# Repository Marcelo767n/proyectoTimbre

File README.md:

# 🔔 Proyecto Timbre Inteligente

Repositorio oficial con la documentación, diseño y código del prototipo de timbre inteligente. Este proyecto se desarrolla para las materias de **Sistemas Embebidos 2** y **Prototipado Rápido**.

---

## 🎯 Objetivo del Proyecto

Diseñar y construir el prototipo de un timbre inteligente basado en una placa de circuito impreso (PCB) personalizada. El sistema captura la presencia de visitantes y gestiona la información de forma remota a través de una interfaz web centralizada.

---

## ⚙️ Arquitectura del Sistema

El proyecto destaca por su capacidad de comunicación remota. Los módulos **no necesitan estar conectados a la misma red Wi-Fi**, ya que la transferencia de datos se realiza a través de Internet.

### 1. Módulo del Timbre (Cliente)
* **Hardware:** ESP32-CAM integrado en una PCB propia diseñada en **KiCad**.
* **Firmware:** Desarrollado en el framework profesional **ESP-IDF** utilizando el entorno de **PlatformIO**.
* **Función:** Al presionar el timbre, el dispositivo se conecta a la red Wi-Fi local (Red A), captura una fotografía del visitante y la envía mediante una petición **HTTP POST** hacia el servidor remoto.

### 2. Módulo de Gestión (Servidor e Interfaz Web)
* **Hardware:** Raspberry Pi.
* **Backend:** Desarrollado en **Python**. Actúa como servidor web central conectado a Internet (Red B) para recibir las peticiones HTTP del timbre y procesar las imágenes.
* **Frontend:** Cuenta con una **interfaz web dedicada** que permite visualizar las fotografías tomadas y consultar los datos de los visitantes en tiempo real.
* **Almacenamiento:** Guarda el historial de visitas de forma estructurada en archivos independientes con formato `.csv` (un archivo `.csv` por cada timbre registrado).

---

## 📊 Datos Registrados

Por cada interacción con el timbre, el sistema procesa y despliega en la interfaz web:
* 📸 Fotografía del visitante.
* 📅 Fecha y hora exacta del evento.
* 🆔 Identificador único del timbre (soporte multi-timbre).

---

## 🛠️ Tecnologías y Herramientas

* **Hardware Base:** ESP32-CAM & Raspberry Pi
* **Diseño Electrónico:** KiCad (Diseño y ruteo de la placa PCB)
* **Entorno de Desarrollo (Firmware):** PlatformIO + ESP-IDF (C/C++)
* **Entorno de Desarrollo (Servidor):** Python
* **Protocolo de Comunicación:** HTTP (Transmisión optimizada de imágenes y metadatos)
* **Base de Datos:** Archivos de texto plano (.CSV) independientes por dispositivo

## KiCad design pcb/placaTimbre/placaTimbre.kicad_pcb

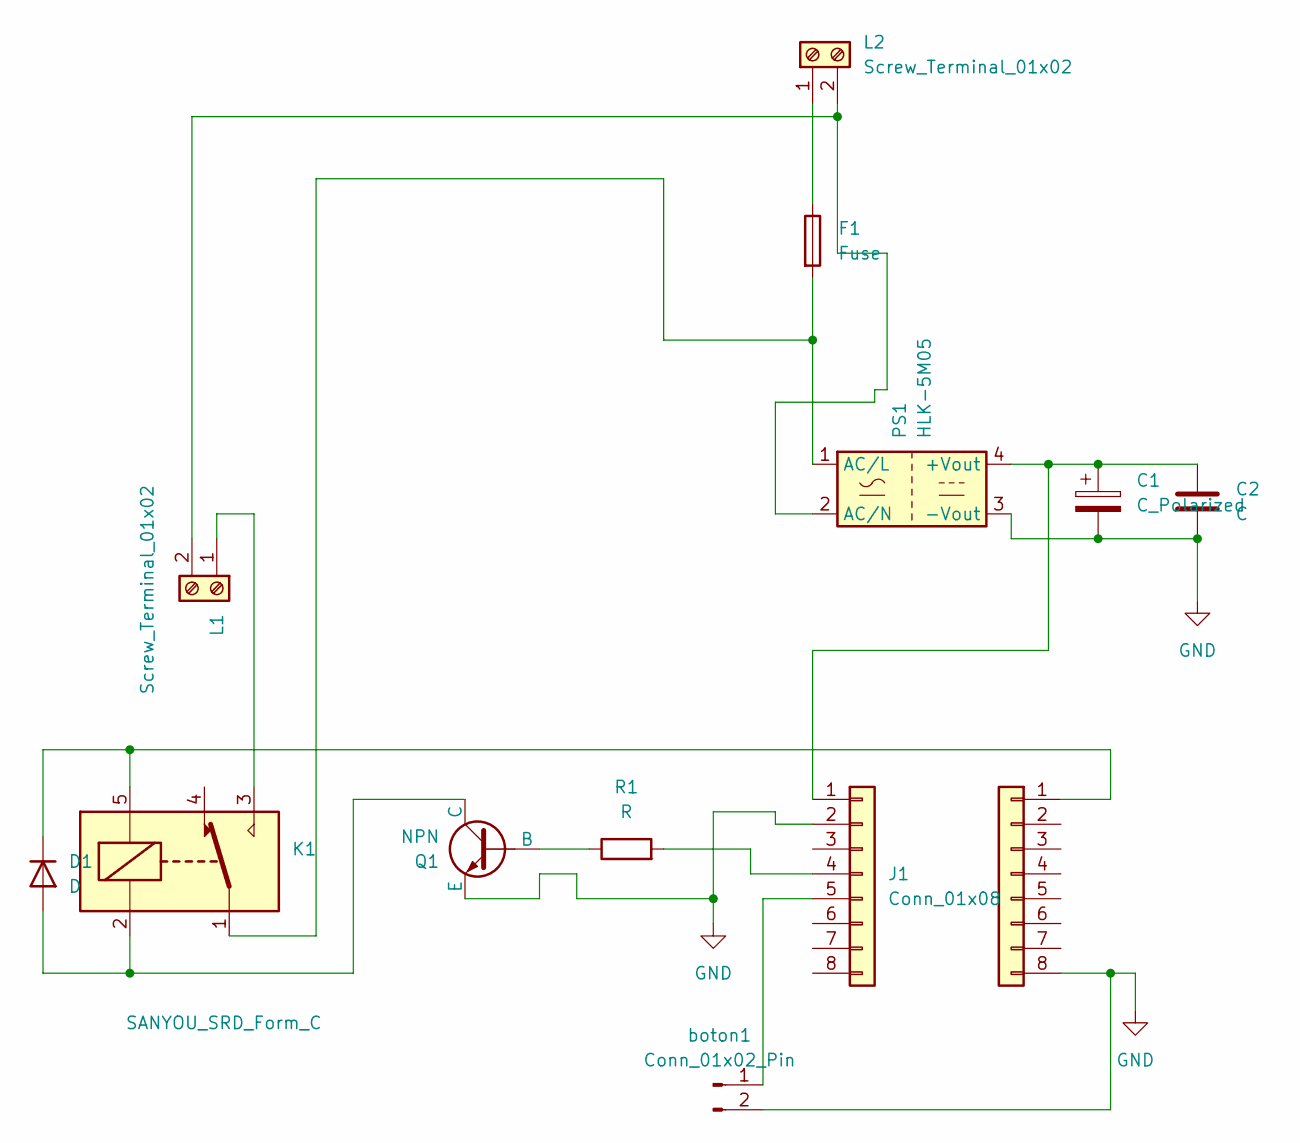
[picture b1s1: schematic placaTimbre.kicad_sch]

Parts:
C1: C_Polarized; CP_Radial_D6.3mm_P2.50mm
C2: C; C_Disc_D5.0mm_W2.5mm_P5.00mm
D1: D; D_DO-41_SOD81_P10.16mm_Horizontal
F1: Fuse; Fuseholder_Clip-5x20mm_Eaton_1A5601-01_Inline_P20.80x6.76mm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
J1, J2: Conn_01x08; PinHeader_1x08_P2.54mm_Vertical
K1: SANYOU_SRD_Form_C; Relay_SPDT_SANYOU_SRD_Series_Form_C
L1, L2: Screw_Terminal_01x02; TerminalBlock_Phoenix_MKDS-1,5-2-5.08_1x02_P5.08mm_Horizont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
PS1: HLK-5M05; Converter_ACDC_Hi-Link_HLK-5Mxx
Q1: NPN; TO-92_Inline_Wide
R1: R; R_Axial_DIN0207_L6.3mm_D2.5mm_P10.16mm_Horizontal
boton1: Conn_01x02_Pin; PinHeader_1x02_P2.54mm_Vertical

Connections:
GND: C1.2, C2.2, J1.2, J2.8, PS1.3 (-Vout), Q1.3 (E), boton1.2
unnamed: D1.2 (A), K1.2, Q1.1 (C)
unnamed: D1.1 (K), J2.1, K1.5
unnamed: C1.1, C2.1, J1.1, PS1.4 (+Vout)
unnamed: J1.4, R1.2
unnamed: J1.5, boton1.1
unnamed: K1.3, L1.1
unnamed: L1.2, L2.2, PS1.2 (AC/N)
unnamed: F1.1, L2.1
unnamed: F1.2, K1.1, PS1.1 (AC/L)
unnamed: Q1.2 (B), R1.1

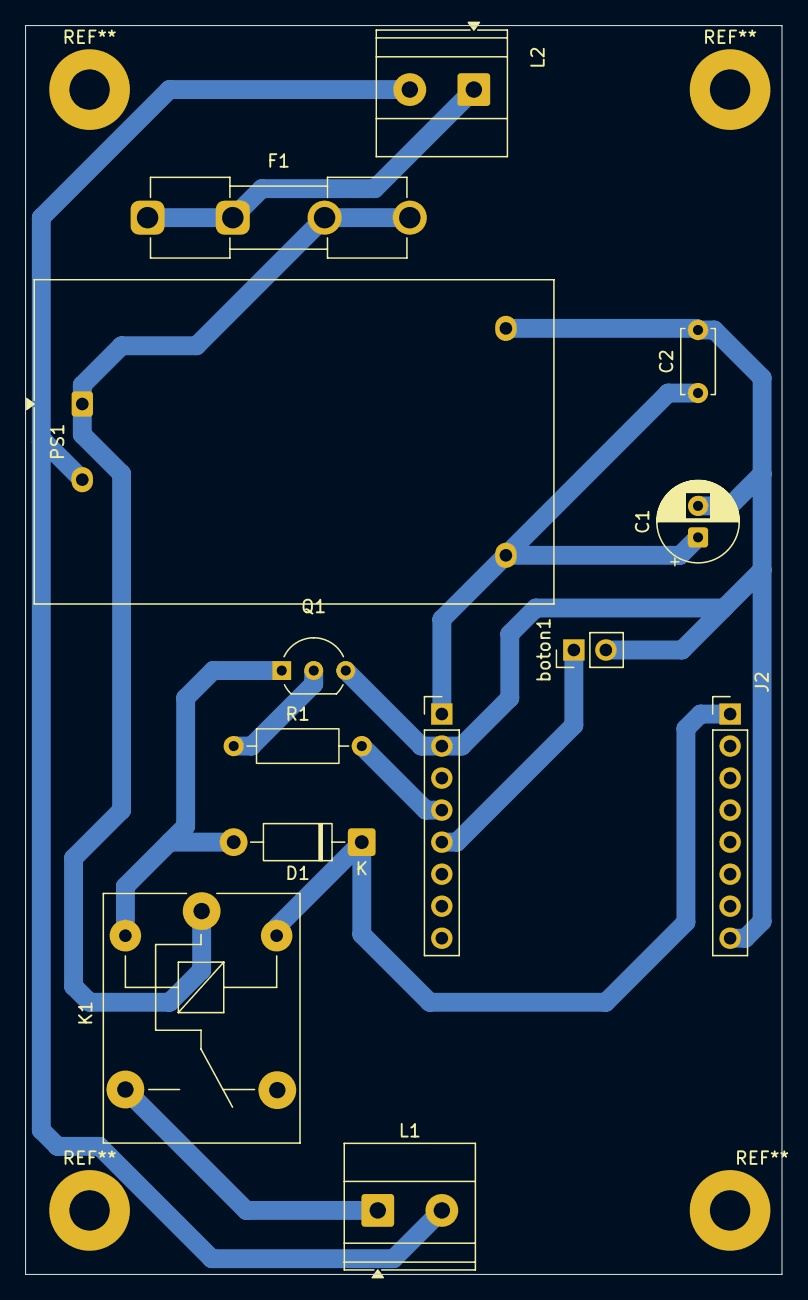
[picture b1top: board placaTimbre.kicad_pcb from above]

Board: 2 copper layers, 60.0 x 99.1 mm, 13 parts (0 on the bottom side), 11 nets.

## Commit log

2026-06-05 creacion de carpetas y diseno de la placa pcb
2026-06-05 creacion del proyecto platformio, readme y gitignore
2026-06-05 prueba de archivos main.c y demas en platformio
2026-06-05 prueba de wifi de esp32 cam
2026-06-05 arreglo de conexion wifi y cambios en archivo .ini
2026-06-05 mejor modularizacion y wifi para usuarios
2026-06-05 mejora de interfaz para usuario wifi
2026-06-05 correccion a la conectividad wifi
2026-06-05 inicializacion de los paquete de camara
2026-06-05 primera foto enviada por http
2026-06-05 organizacion de carpetas
2026-06-06 cambios en la placa y diseno de carcasa
2026-06-06 particiones de memoria, envio de fotos remotante
2026-06-06 primera foto enviada de esp32 a raspberry, instalacion de cloudflare
2026-06-08 actualizacion de codigo
2026-06-08 cambio de red wifi
